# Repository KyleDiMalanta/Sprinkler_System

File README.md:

Folders proto1 - proto4 contains Arduino Code aimed at integrating the whole system (user interface and pump/solenoid actions).
Other folders include tests which isolate the pumps, LCD, and transistor tests.
The watering_pcb folder has the most up to date KiCad files for the PCB.

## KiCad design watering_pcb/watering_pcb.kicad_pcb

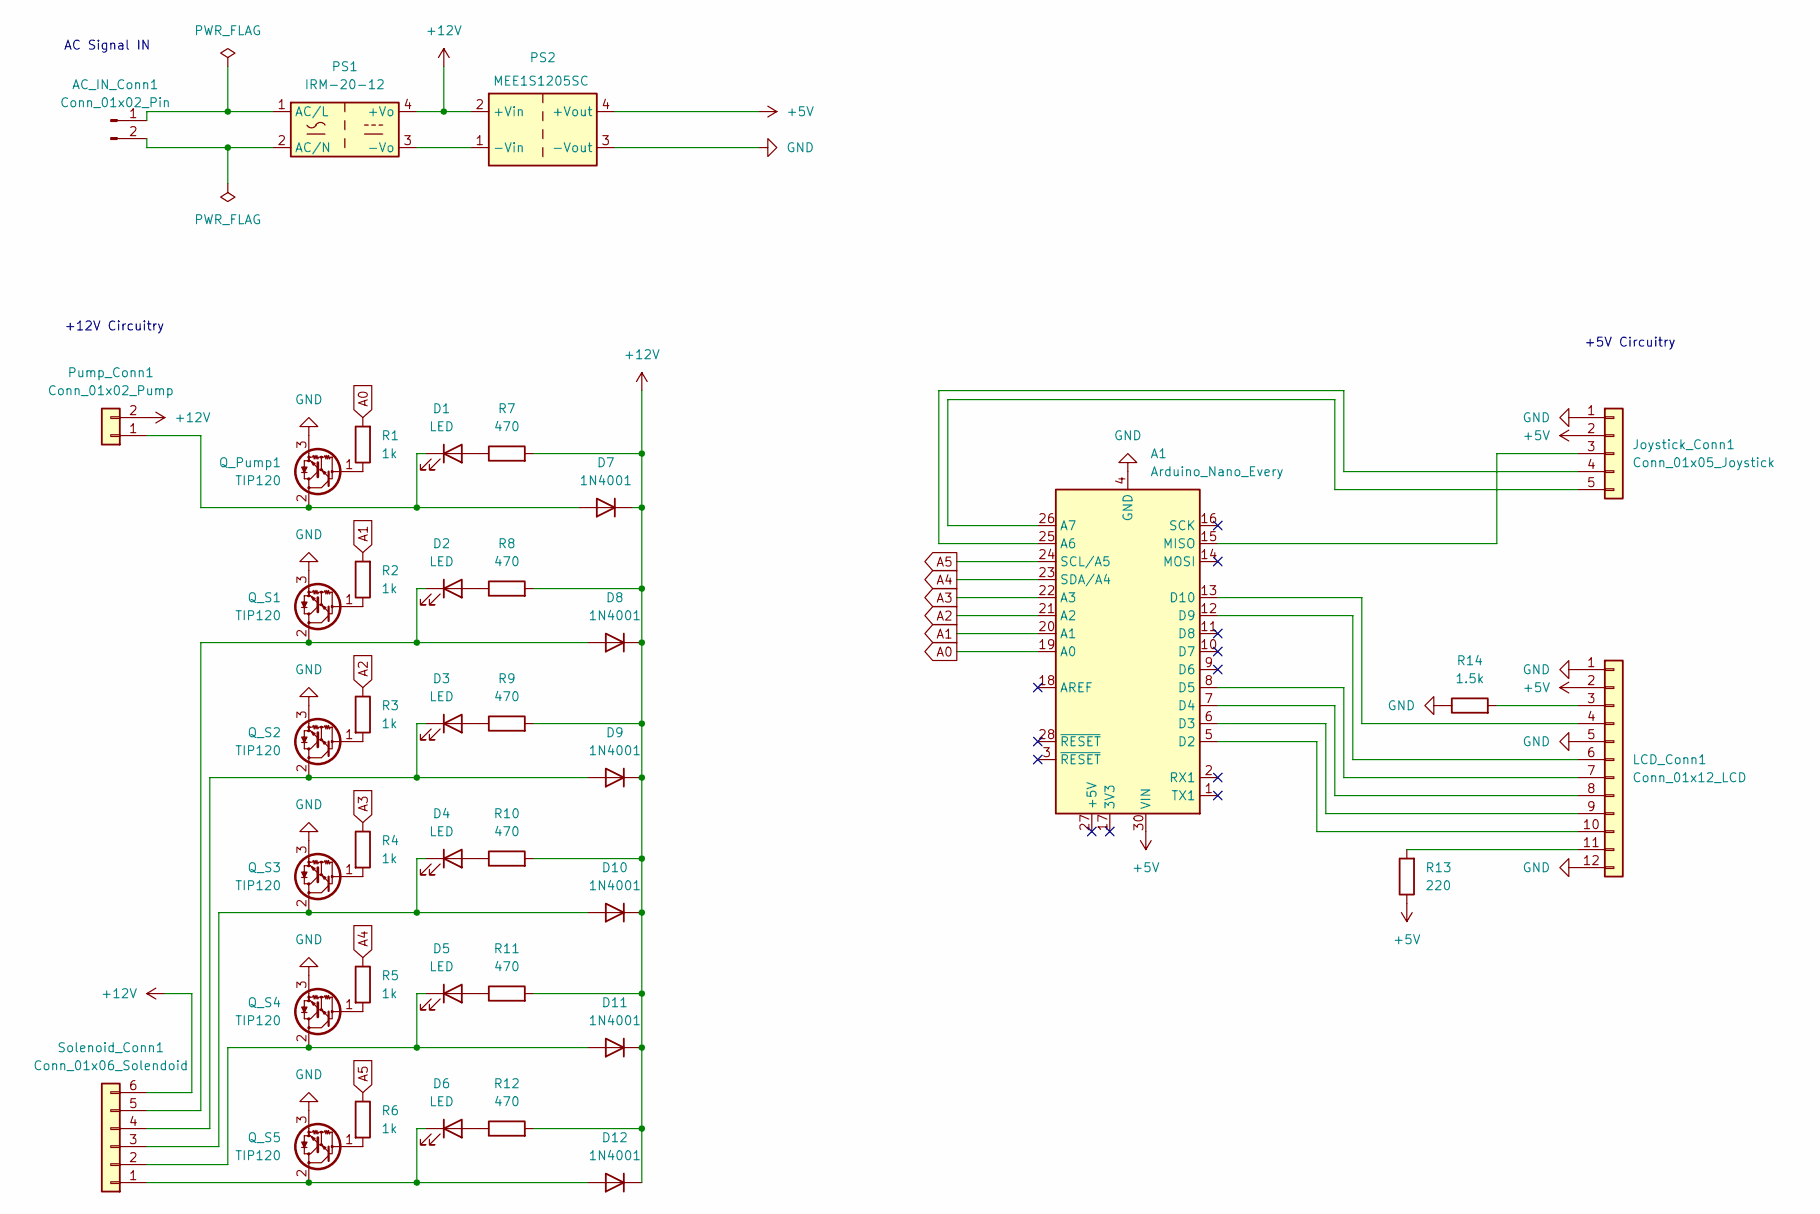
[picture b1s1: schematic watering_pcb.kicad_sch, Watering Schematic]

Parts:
A1: Arduino_Nano_Every; Arduino_Nano
AC_IN_Conn1: Conn_01x02_Pin; TerminalBlock_Phoenix_MKDS-3-2-5.08_1x02_P5.08mm_Horizontal
D1, D2, D3, D4, D5, D6: LED; LED_D5.0mm
D7, D8, D9, D10, D11, D12: 1N4001; D_DO-41_SOD81_P10.16mm_Horizontal
Joystick_Conn1: Conn_01x05_Joystick; PinHeader_1x05_P2.54mm_Vertical
LCD_Conn1: Conn_01x12_LCD; PinHeader_1x12_P2.54mm_Vertical
PS1: IRM-20-12; Converter_ACDC_MeanWell_IRM-20-xx_THT
PS2: MEE1S1205SC; Converter_DCDC_Murata_MEE1SxxxxSC_THT
Pump_Conn1: Conn_01x02_Pump; TerminalBlock_Phoenix_MKDS-3-2-5.08_1x02_P5.08mm_Horizontal
Q_Pump1: TIP120; TO-220-3_Vertical
Q_S1, Q_S2, Q_S3, Q_S4, Q_S5: TIP120; TO-220-3_Vertical
R1, R2, R3, R4, R5, R6: 1k; R_Axial_DIN0207_L6.3mm_D2.5mm_P7.62mm_Horizontal
R7, R8, R9, R10, R11, R12: 470; R_Axial_DIN0207_L6.3mm_D2.5mm_P7.62mm_Horizontal
R13: 220; R_Axial_DIN0207_L6.3mm_D2.5mm_P7.62mm_Horizontal
R14: 1.5k; R_Axial_DIN0207_L6.3mm_D2.5mm_P7.62mm_Horizontal
Solenoid_Conn1: Conn_01x06_Solendoid; PinHeader_1x06_P2.54mm_Vertical

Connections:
+5V: A1.30 (VIN), Joystick_Conn1.2 (+5V), LCD_Conn1.2 (VDD), PS2.4 (+Vout), R13.1
+12V: D7.1 (K), D8.1 (K), D9.1 (K), D10.1 (K), D11.1 (K), D12.1 (K), PS1.4 (+Vo), PS2.2 (+Vin), Pump_Conn1.2 (+12V), R7.2, R8.2, R9.2, R10.2, R11.2, R12.2, Solenoid_Conn1.6 (S1)
A0: A1.19 (A0), R1.2
A1: A1.20 (A1), R2.2
A2: A1.21 (A2), R3.1
A3: A1.22 (A3), R4.1
A4: A1.23 (SDA/A4), R5.1
A5: A1.24 (SCL/A5), R6.1
GND: A1.4 (GND), A1.29 (GND), Joystick_Conn1.1 (Ground), LCD_Conn1.1 (VSS), LCD_Conn1.5 (RW), LCD_Conn1.12 (K), PS2.3 (-Vout), Q_Pump1.3 (E), Q_S1.3 (E), Q_S2.3 (E), Q_S3.3 (E), Q_S4.3 (E), Q_S5.3 (E), R14.1
unnamed: A1.25 (A6), Joystick_Conn1.4 (X)
unnamed: A1.26 (A7), Joystick_Conn1.5 (Y)
unnamed: A1.5 (D2), LCD_Conn1.10 (D7)
unnamed: A1.6 (D3), LCD_Conn1.9 (D6)
unnamed: A1.7 (D4), LCD_Conn1.8 (D5)
unnamed: A1.8 (D5), LCD_Conn1.7 (D4)
unnamed: A1.12 (D9), LCD_Conn1.6 (E)
unnamed: A1.13 (D10), LCD_Conn1.4 (RS)
unnamed: A1.15 (MISO), Joystick_Conn1.3 (Button)
unnamed: AC_IN_Conn1.1, PS1.1 (AC/L)
unnamed: AC_IN_Conn1.2, PS1.2 (AC/N)
unnamed: D1.2 (A), R7.1
unnamed: D1.1 (K), D7.2 (A), Pump_Conn1.1 (Pump), Q_Pump1.2 (C)
unnamed: D2.2 (A), R8.1
unnamed: D2.1 (K), D8.2 (A), Q_S1.2 (C), Solenoid_Conn1.5 (S2)
unnamed: D3.2 (A), R9.1
unnamed: D3.1 (K), D9.2 (A), Q_S2.2 (C), Solenoid_Conn1.4 (S3)
unnamed: D4.2 (A), R10.1
unnamed: D5.2 (A), R11.1
unnamed: D6.2 (A), R12.1
unnamed: D4.1 (K), D10.2 (A), Q_S3.2 (C), Solenoid_Conn1.3 (S4)
unnamed: D5.1 (K), D11.2 (A), Q_S4.2 (C), Solenoid_Conn1.2 (S5)
unnamed: D6.1 (K), D12.2 (A), Q_S5.2 (C), Solenoid_Conn1.1 (+12V)
unnamed: LCD_Conn1.11 (A), R13.2
unnamed: LCD_Conn1.3 (V0), R14.2
unnamed: PS1.3 (-Vo), PS2.1 (-Vin)
unnamed: Q_Pump1.1 (B), R1.1
unnamed: Q_S1.1 (B), R2.1
unnamed: Q_S2.1 (B), R3.2
unnamed: Q_S3.1 (B), R4.2
unnamed: Q_S4.1 (B), R5.2
unnamed: Q_S5.1 (B), R6.2

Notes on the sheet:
+12V Circuitry
AC Signal IN
+5V Circuitry

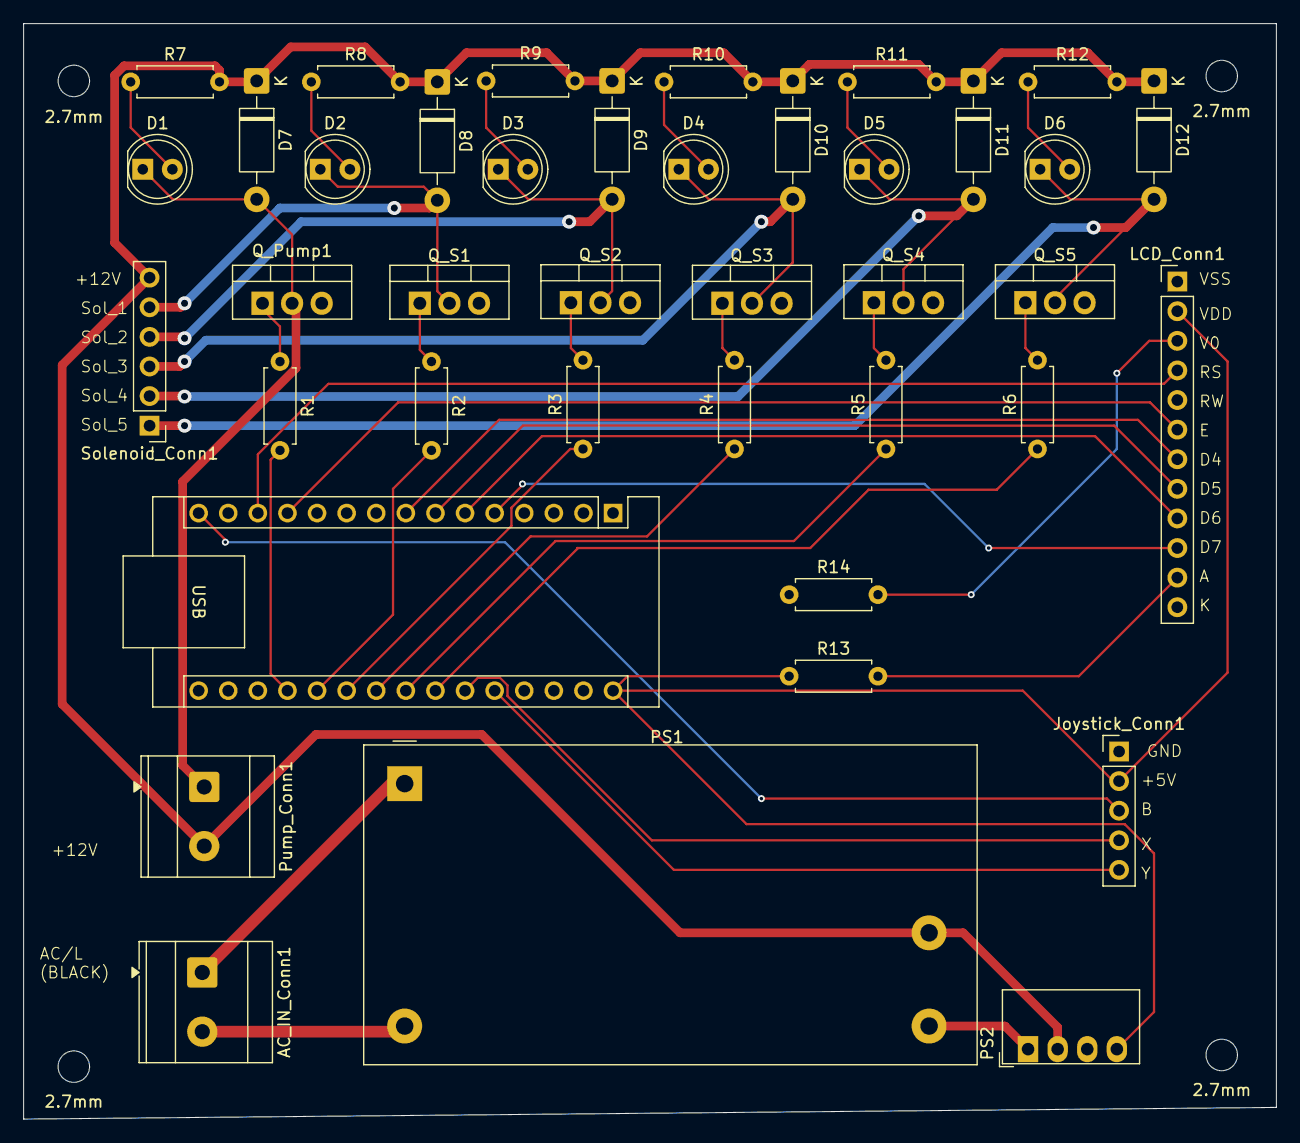
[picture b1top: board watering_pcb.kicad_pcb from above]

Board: 2 copper layers, 107.5 x 94.0 mm, 44 parts (0 on the bottom side), 41 nets.

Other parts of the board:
2.7mm, 2.7mm#2, 2.7mm#3, 2.7mm#4: 2.7mm; MountingHole_2.7mm

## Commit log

2026-03-03 Add all Arduino code and KiCad files used for testing and devlopment
2026-03-03 Add project structure and folder descriptions to README
2026-03-03 Changed readme format
